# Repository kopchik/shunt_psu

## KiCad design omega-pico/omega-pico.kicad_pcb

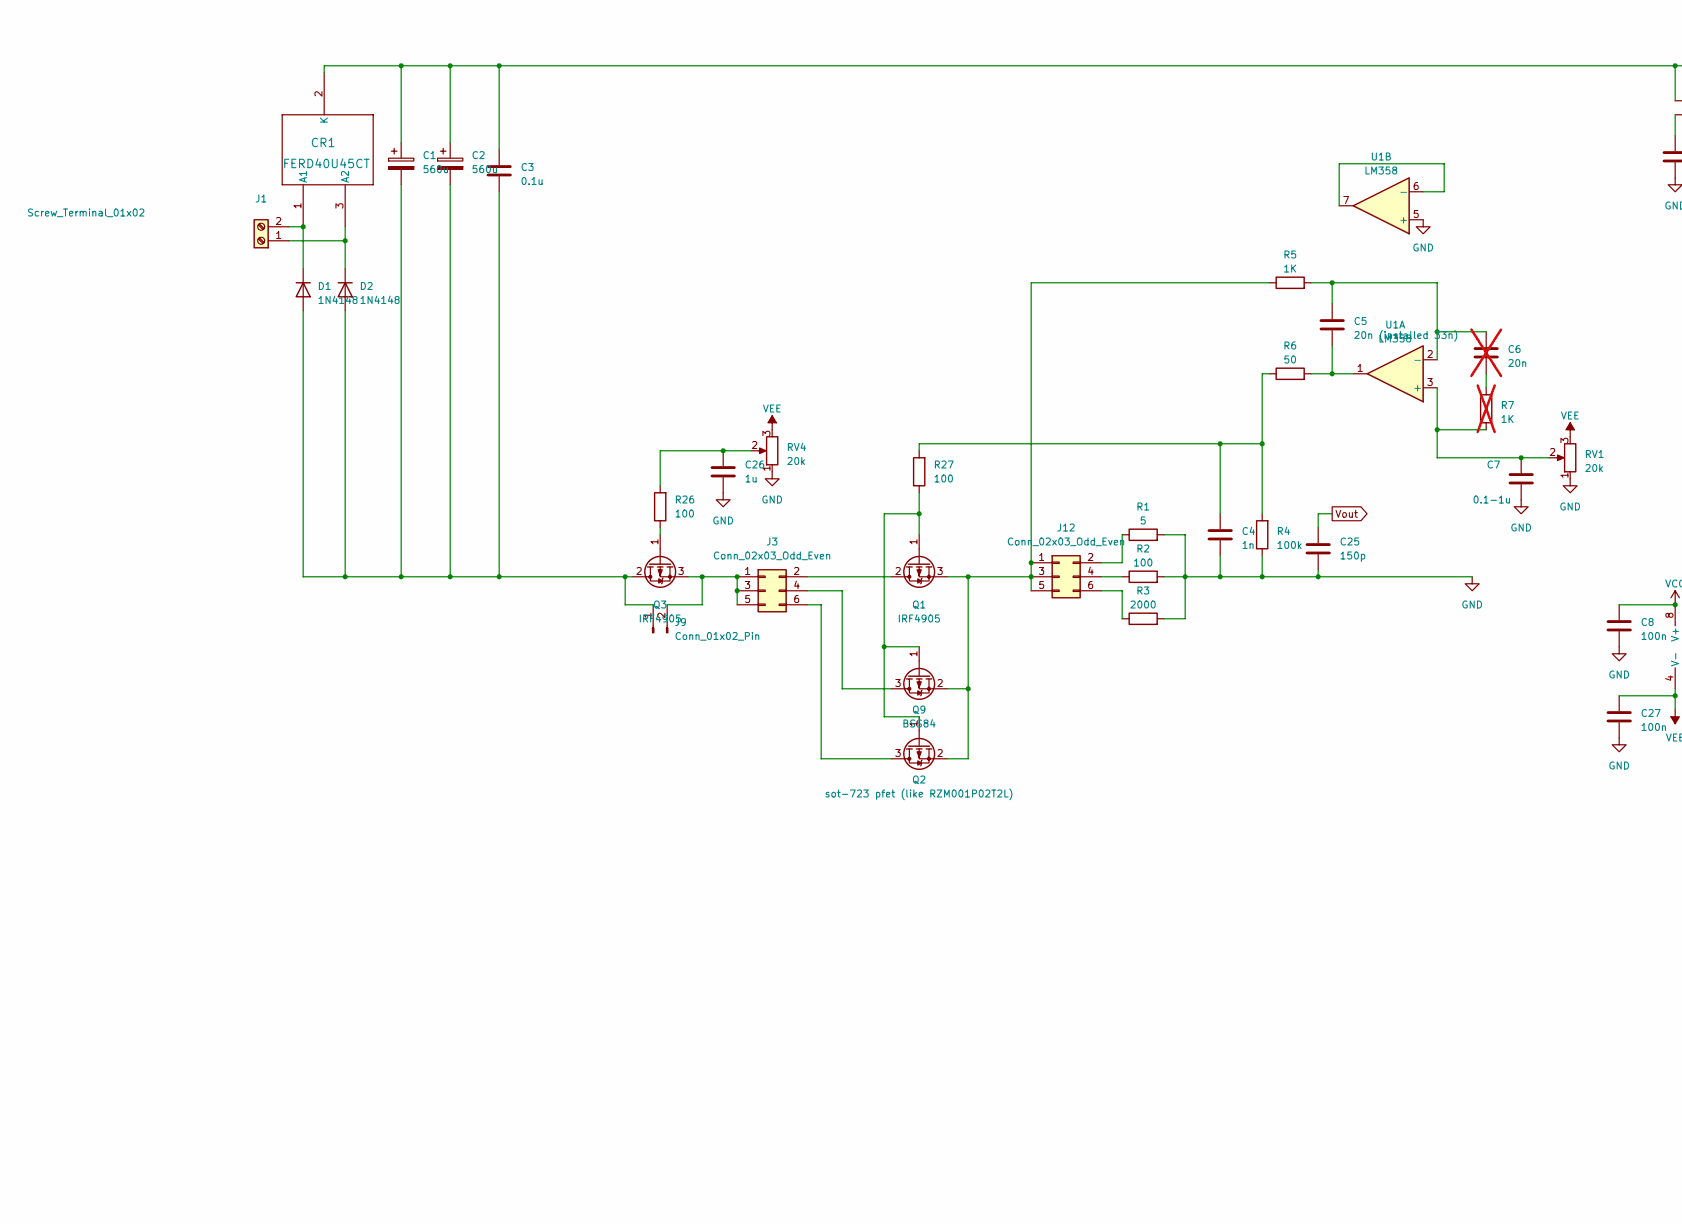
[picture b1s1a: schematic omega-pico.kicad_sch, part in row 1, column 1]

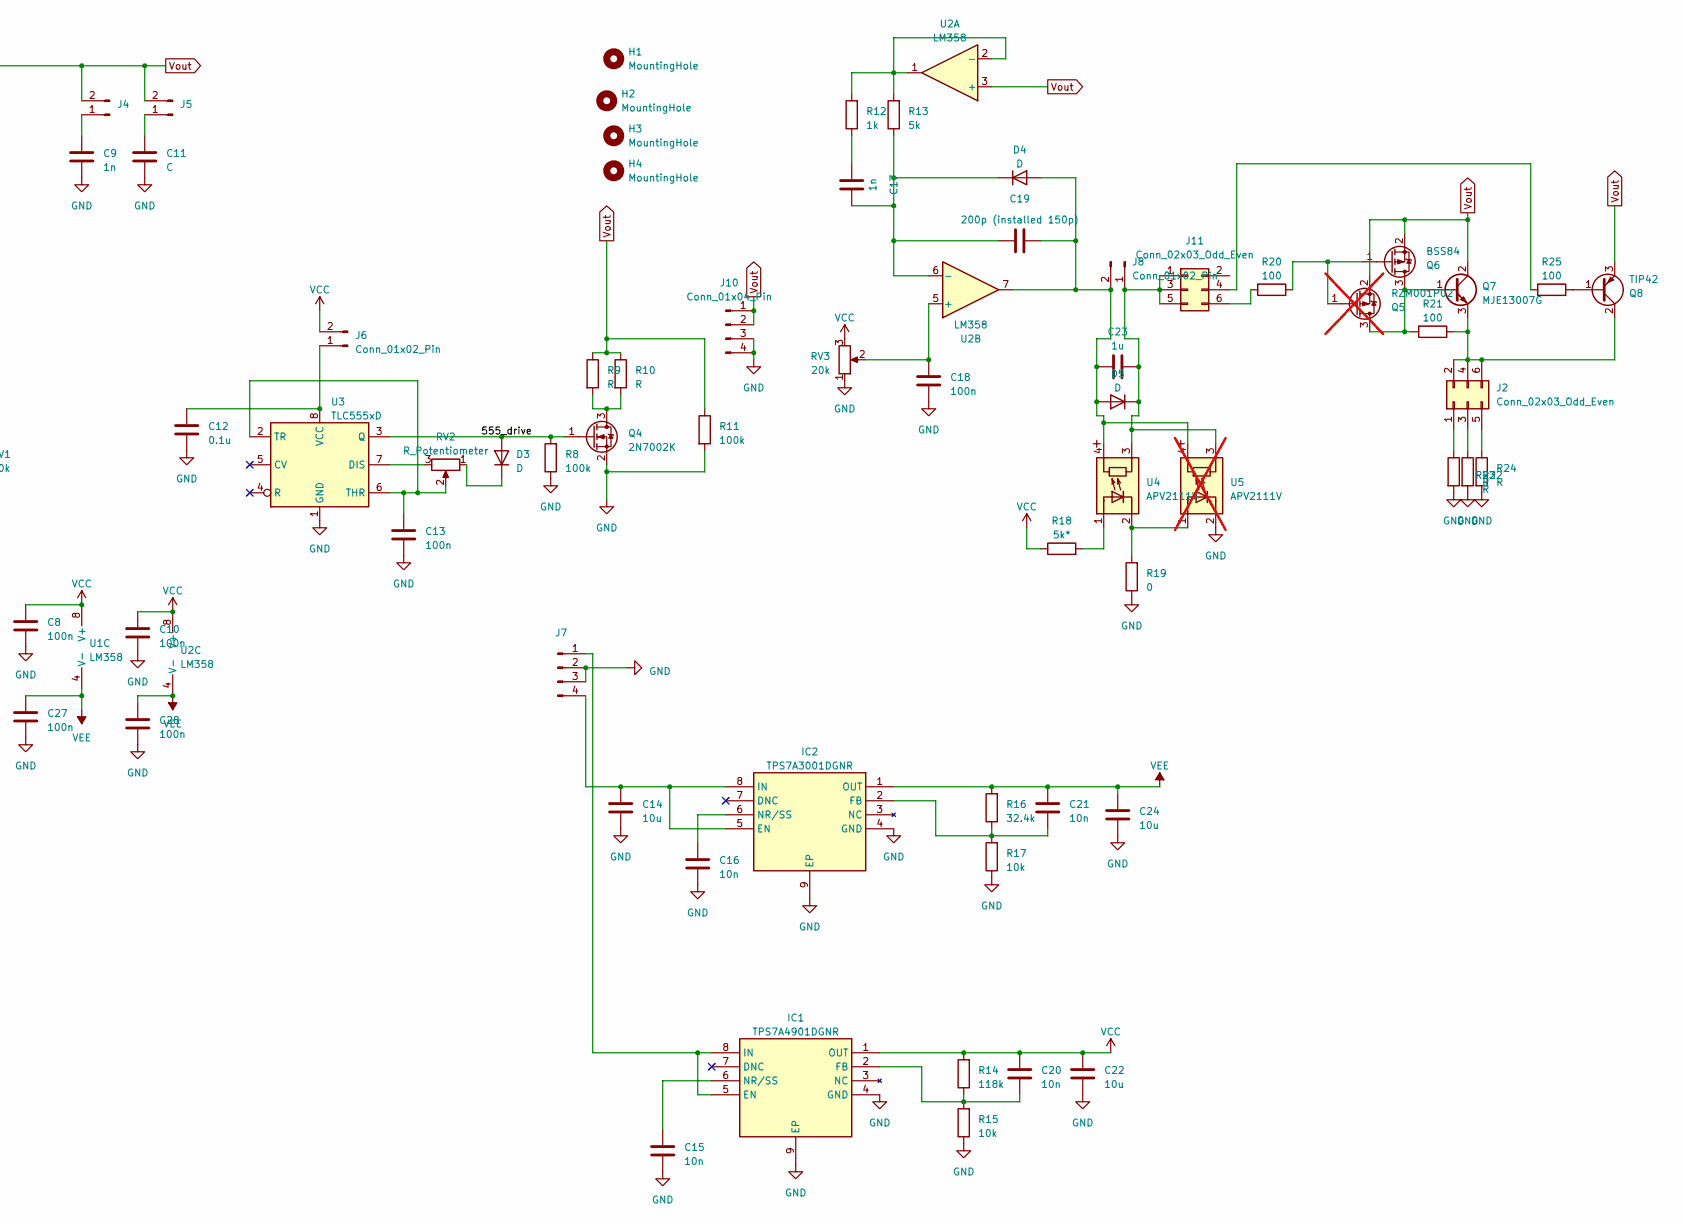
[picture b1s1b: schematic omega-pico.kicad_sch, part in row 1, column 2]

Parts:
C1, C2: 560u; CP_Radial_D10.0mm_P2.50mm_P5.00mm
C3, C12: 0.1u; C_0805_2012Metric
C4: 1n; C_0603_1608Metric
C5: 20n (installed 33n); C_0603_1608Metric
C6: 20n; C_0603_1608Metric; not fitted
C7: 0.1-1u; C_0603_1608Metric
C8, C10, C27, C28: 100n; C_0603_1608Metric
C9, C17: 1n; C_0805_2012Metric
C11: C; CP_Radial_D10.0mm_P2.50mm_P5.00mm
C13, C18: 100n; C_0805_2012Metric
C14, C22, C24: 10u; C_0603_1608Metric
C15, C16, C20, C21: 10n; C_0603_1608Metric
C19: 200p (installed 150p); C_0805_2012Metric
C23: 1u; C_0805_2012Metric
C25: 150p; C_0603_1608Metric
C26: 1u; C_0603_1608Metric
CR1: FERD40U45CT; TO-220-3_Vertical
D1, D2: 1N4148; D_DO-35_SOD27_P7.62mm_Horizontal
D3, D4: D; D_0805_2012Metric
D5: D; D_T-1_P2.54mm_Vertical_AnodeUp
H1, H2, H3, H4: MountingHole; MountingHole_3.2mm_M3
IC1: TPS7A4901DGNR; SOP65P490X110-9N; Mouser Part Number 595-TPS7A4901DGNR
IC2: TPS7A3001DGNR; SOP65P490X110-9N; Mouser Part Number 595-TPS7A3001DGNR
J1: Screw_Terminal_01x02; TerminalBlock_bornier-2_P5.08mm
J2, J3, J11, J12: Conn_02x03_Odd_Even; PinHeader_2x03_P2.54mm_Vertical
J4, J5, J6, J8, J9: Conn_01x02_Pin; PinHeader_1x02_P2.54mm_Vertical
J7, J10: Conn_01x04_Pin; PinHeader_1x04_P2.54mm_Vertical
Q1, Q3: IRF4905; TO-220-3_Vertical
Q2: sot-723 pfet (like RZM001P02T2L); SOT-723
Q4: 2N7002K; SOT-23
Q5: RZM001P02; SOT-723; not fitted
Q6, Q9: BSS84; SOT-23
Q7: MJE13007G; TO-220-3_Vertical
Q8: TIP42; TO-220-3_Vertical
R1: 5; R_Axial_DIN0207_L6.3mm_D2.5mm_P5.08mm_Vertical
R2, R20, R21, R25, R26, R27: 100; R_0603_1608Metric
R3: 2000; R_0603_1608Metric
R4, R8: 100k; R_0603_1608Metric
R5: 1K; R_0603_1608Metric
R6: 50; R_0603_1608Metric
R7: 1K; R_0603_1608Metric; not fitted
R9, R10, R22, R23, R24: R; R_1206_3216Metric
R11: 100k; R_1206_3216Metric
R12: 1k; R_0603_1608Metric
R13: 5k; R_0603_1608Metric
R14: 118k; R_0603_1608Metric
R15, R17: 10k; R_0603_1608Metric
R16: 32.4k; R_0603_1608Metric
R18: 5k*; R_0603_1608Metric
R19: 0; R_0603_1608Metric
RV1, RV3, RV4: 20k; Potentiometer_Bourns_3296W_Vertical
RV2: R_Potentiometer; Potentiometer_Bourns_3296W_Vertical
U1, U2: LM358; SO-8_3.9x4.9mm_P1.27mm
U3: TLC555xD; SOIC-8_3.9x4.9mm_P1.27mm
U4: APV2111V; Panasonic_APV-AQY_SSOP-4_4.45x2.65mm_P1.27mm
U5: APV2111V; Panasonic_APV-AQY_SSOP-4_4.45x2.65mm_P1.27mm; not fitted

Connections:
/555_drive: D3.2 (A), Q4.1 (G), R8.2, U3.3 (Q)
GND: C4.2, C7.2, C8.2, C9.2, C10.2, C11.2, C12.2, C13.2, C14.2, C15.2, C16.2, C18.2, C22.2, C24.2, C25.1, C26.1, C27.2, C28.2, IC1.4 (GND), IC1.9 (EP), IC2.4 (GND), IC2.9 (EP), J7.2, J7.3, J10.3, J10.4, Q4.2 (S), R1.2, R2.2, R3.2, R4.1, R8.1, R11.2, R15.1, R17.1, R19.1, R22.2, R23.2, R24.2, RV1.1, RV3.1, RV4.1, U1.5 (+), U3.1 (GND), U5.2 (K)
unnamed: C4.1, R4.2, R6.1, R27.2
unnamed: C5.2, R6.2, U1.1
unnamed: C6.2, R7.2
unnamed: C17.1, R12.1
unnamed: C26.2, R26.2, RV4.2
unnamed: CR1.1 (A1), D1.1 (K), J1.2
unnamed: CR1.3 (A2), D2.1 (K), J1.1
unnamed: C1.2, C2.2, C3.2, D1.2 (A), D2.2 (A), J9.1, Q3.2 (D)
unnamed: D3.1 (K), RV2.1
unnamed: C19.2, C23.1, D4.2 (A), D5.2 (A), J8.2, U2.7, U4.4 (R), U5.4 (R)
unnamed: C17.2, C19.1, D4.1 (K), R13.1, U2.6 (-)
unnamed: C23.2, D5.1 (K), J8.1, J11.1, J11.3, J11.5, U4.3 (R), U5.3 (R)
unnamed: IC1.5 (EN), IC1.8 (IN), J7.1
unnamed: C20.2, IC1.2 (FB), R14.1, R15.2
unnamed: C15.1, IC1.6 (NR/SS)
unnamed: C14.1, IC2.5 (EN), IC2.8 (IN), J7.4
unnamed: C21.2, IC2.2 (FB), R16.1, R17.2
unnamed: C16.1, IC2.6 (NR/SS)
unnamed: J2.1, R22.1
unnamed: J2.2, J2.4, J2.6, Q7.3 (E), Q8.2 (C), R21.1
unnamed: J2.3, R23.1
unnamed: J2.5, R24.1
unnamed: J3.1, J3.3, J3.5, J9.2, Q3.3 (S)
unnamed: J3.2, Q1.2 (D)
unnamed: J3.4, Q9.3 (D)
unnamed: J3.6, Q2.3 (D)
unnamed: C9.1, J4.1
unnamed: C11.1, J5.1
unnamed: C12.1, J6.1, U3.8 (VCC)
unnamed: J11.4, R25.2
unnamed: J11.6, R20.2
unnamed: J12.1, J12.3, J12.5, Q1.3 (S), Q2.2 (S), Q9.2 (S), R5.1
unnamed: J12.2, R1.1
unnamed: J12.4, R2.1
unnamed: J12.6, R3.1
unnamed: Q1.1 (G), Q2.1 (G), Q9.1 (G), R27.1
unnamed: Q3.1 (G), R26.1
unnamed: Q4.3 (D), R9.2, R10.2
unnamed: Q5.3 (D), Q6.3 (D), Q7.1 (B), R21.2
unnamed: Q5.1 (G), Q6.1 (G), R20.1
unnamed: Q8.1 (B), R25.1
unnamed: C7.1, R7.1, RV1.2, U1.3 (+)
unnamed: C5.1, C6.1, R5.2, U1.2 (-)
unnamed: U1.6 (-), U1.7
unnamed: R12.2, R13.2, U2.1, U2.2 (-)
unnamed: C18.1, RV3.2, U2.5 (+)
unnamed: RV2.3, U3.7 (DIS)
unnamed: C13.1, RV2.2, U3.2 (TR), U3.6 (THR)
unnamed: R18.2, U4.1 (A)
unnamed: R19.2, U4.2 (K), U5.1 (A)
VCC: C8.1, C10.1, C20.1, C22.1, IC1.1 (OUT), J6.2, R14.2, R18.1, RV3.3, U1.8 (V+), U2.8 (V+)
VEE: C21.1, C24.1, C27.1, C28.1, IC2.1 (OUT), R16.2, RV1.3, RV4.3, U1.4 (V-), U2.4 (V-)
Vout: C1.1, C2.1, C3.1, C25.2, CR1.2 (K), J4.2, J5.2, J10.1, J10.2, Q5.2 (S), Q6.2 (S), Q7.2 (C), Q8.3 (E), R9.1, R10.1, R11.1, U2.3 (+)

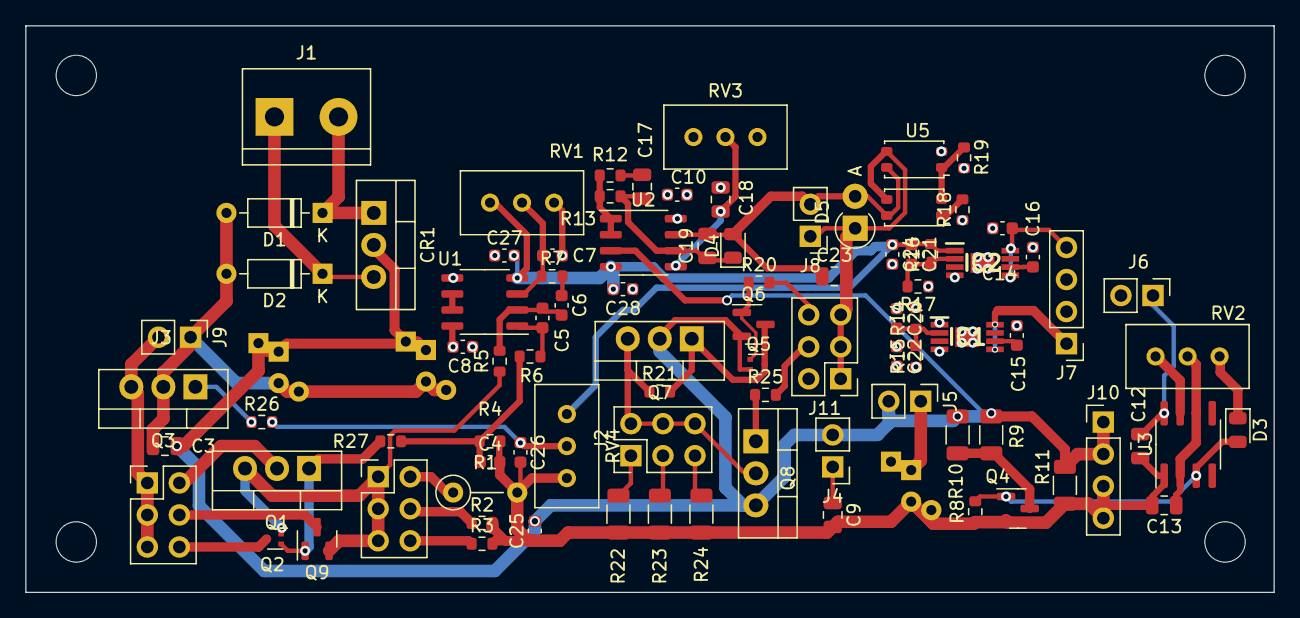
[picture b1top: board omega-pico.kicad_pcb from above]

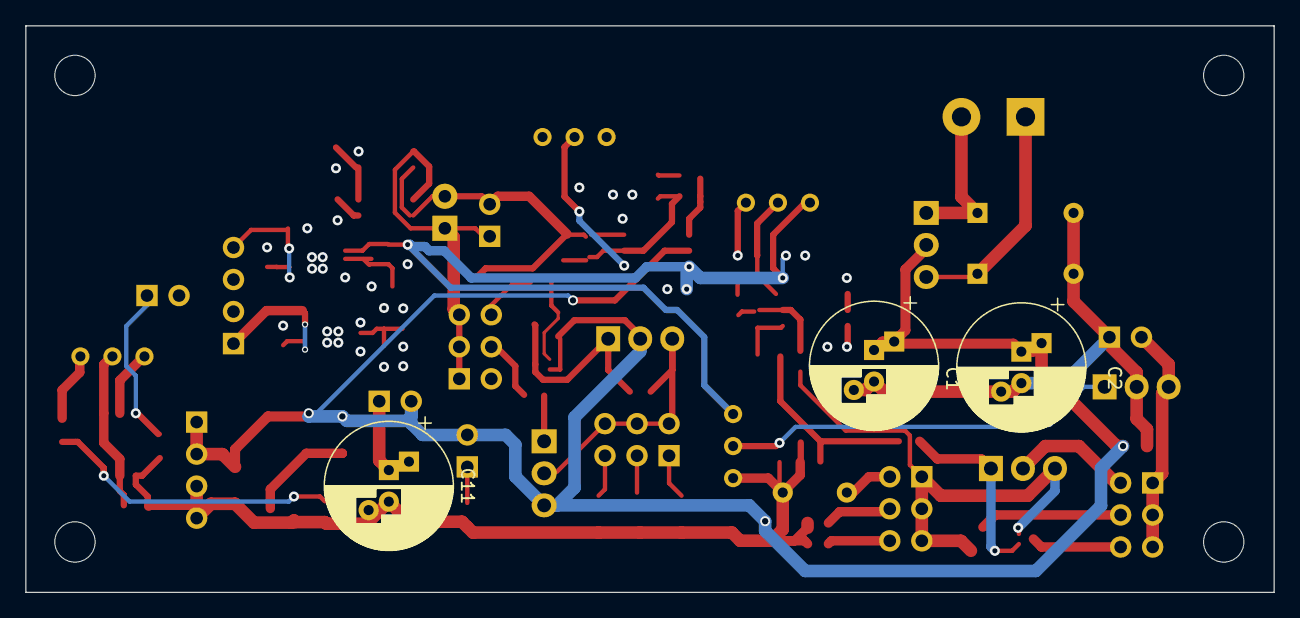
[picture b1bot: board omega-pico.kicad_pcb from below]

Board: 4 copper layers, 99.0 x 44.9 mm, 97 parts (3 on the bottom side), 55 nets.

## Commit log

2023-07-30 omega-pico test pcb
